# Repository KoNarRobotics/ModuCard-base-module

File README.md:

# ModuCard Base Module

This repository provides a template design for creating modules in the ModuCard system. Each module is designed to seamlessly interface with the [ModuCard backplane](https://github.com/KoNarRobotics/ModuCard-backplane), enabling a modular and expandable robotics platform.

## Used tools:

## Features:

### Power section
- **Input voltage:** 12V from the backplane.  
- **Output voltage:** 3.3V @ 0.5A.

### ST-LINK
- Built-in **ST-LINK** connected to the backplane via USB interface.  
- Enables programming and debugging of the onboard MCU.

### CAN interface
- Two independent CAN buses: **CAN1** and **CAN2**.  
- Both connect with the backplane to facilitate communication between the onboard MCU and other modules in the system.

# How to Create a new module from this template
1. **Create a new repository**
2. **Copy files from this repository** to your new repository.  
3. **Rename the files:**
   - `base-module.kicad_pcb` → `<your-board-name>.kicad_pcb`
   - `base-module.kicad_sch` → `<your-board-name>.kicad_sch`
   - `base-module.kicad_pro` → `<your-board-name>.kicad_pro`
4. **Open the project** in KiCad.  
5. **Update page settings** in the schematic and PCB:
   - Change the **Title** to `ModuCard <your project name>`.  
   - Edit **Comment 2** to include your name in the `<author>` field.
6. Enjoy implementing your project!

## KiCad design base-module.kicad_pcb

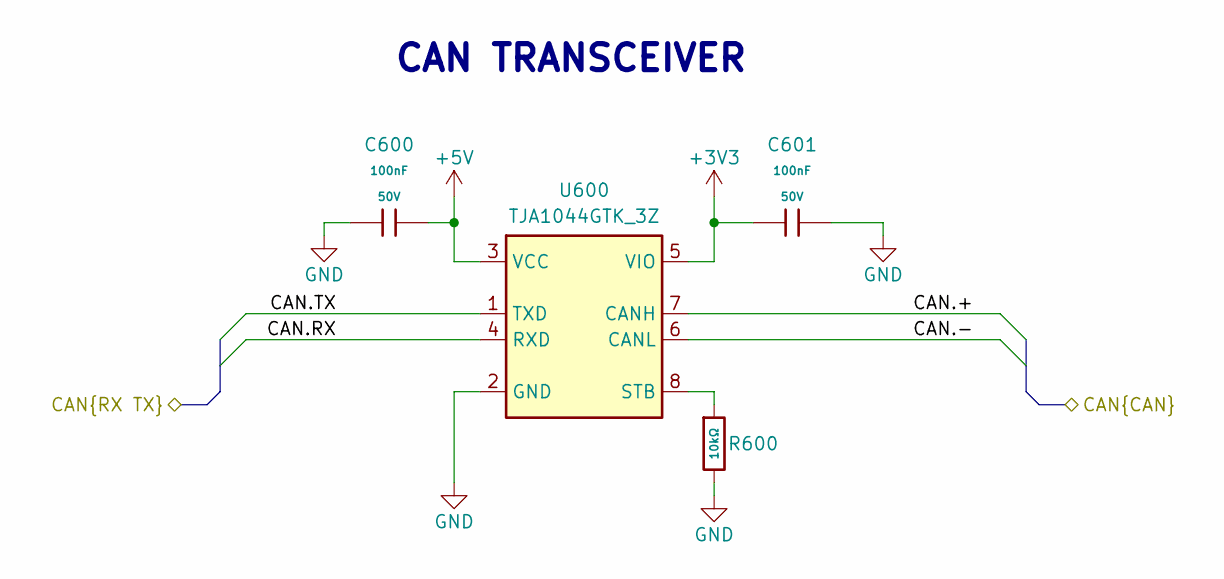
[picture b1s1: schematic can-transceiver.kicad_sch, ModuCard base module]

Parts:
C600, C601: 100nF; C_0402; Voltage Rated 50V; Tolerance ±10%; Part CL05B104KB54PNC; LCSC C307331
R600: 10kΩ; R_0402; Overload Voltage (Max) 50V; Tolerance ±1%; Part 0402WGF1002TCE; LCSC C25744
U600: TJA1044GTK_3Z; HVSON-8-1EP_3x3mm_P0.65mm_EP1.6x2.4mm; Manufacturer_Part_Number TJA1044GTK/3Z

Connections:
+3V3: C601.1, U600.5 (VIO); also elsewhere on the board
+5V: C600.2, U600.3 (VCC); also elsewhere on the board
/Backplane/CAN2.+: U600.7 (CANH); also elsewhere on the board
/Backplane/CAN2.-: U600.6 (CANL); also elsewhere on the board
/CAN transceiver 2/CAN.RX: U600.4 (RXD); also elsewhere on the board
/CAN transceiver 2/CAN.TX: U600.1 (TXD); also elsewhere on the board
GND: C600.1, C601.2, R600.2, U600.2 (GND), U600.9 (EP); also elsewhere on the board
unnamed: R600.1, U600.8 (STB)

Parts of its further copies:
C500, C501: 100nF; C_0402; Voltage Rated 50V; Tolerance ±10%; Part CL05B104KB54PNC; LCSC C307331
R500: 10kΩ; R_0402; Overload Voltage (Max) 50V; Tolerance ±1%; Part 0402WGF1002TCE; LCSC C25744
U500: TJA1044GTK_3Z; HVSON-8-1EP_3x3mm_P0.65mm_EP1.6x2.4mm; Manufacturer_Part_Number TJA1044GTK/3Z

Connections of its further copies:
+3V3: C501.1, U500.5 (VIO); also elsewhere on the board
+5V: C500.2, U500.3 (VCC); also elsewhere on the board
/Backplane/CAN1.+: U500.7 (CANH); also elsewhere on the board
/Backplane/CAN1.-: U500.6 (CANL); also elsewhere on the board
/CAN transceiver 1/CAN.RX: U500.4 (RXD); also elsewhere on the board
/CAN transceiver 1/CAN.TX: U500.1 (TXD); also elsewhere on the board
GND: C500.1, C501.2, R500.2, U500.2 (GND), U500.9 (EP); also elsewhere on the board
unnamed: R500.1, U500.8 (STB)

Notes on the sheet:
CAN TRANSCEIVER

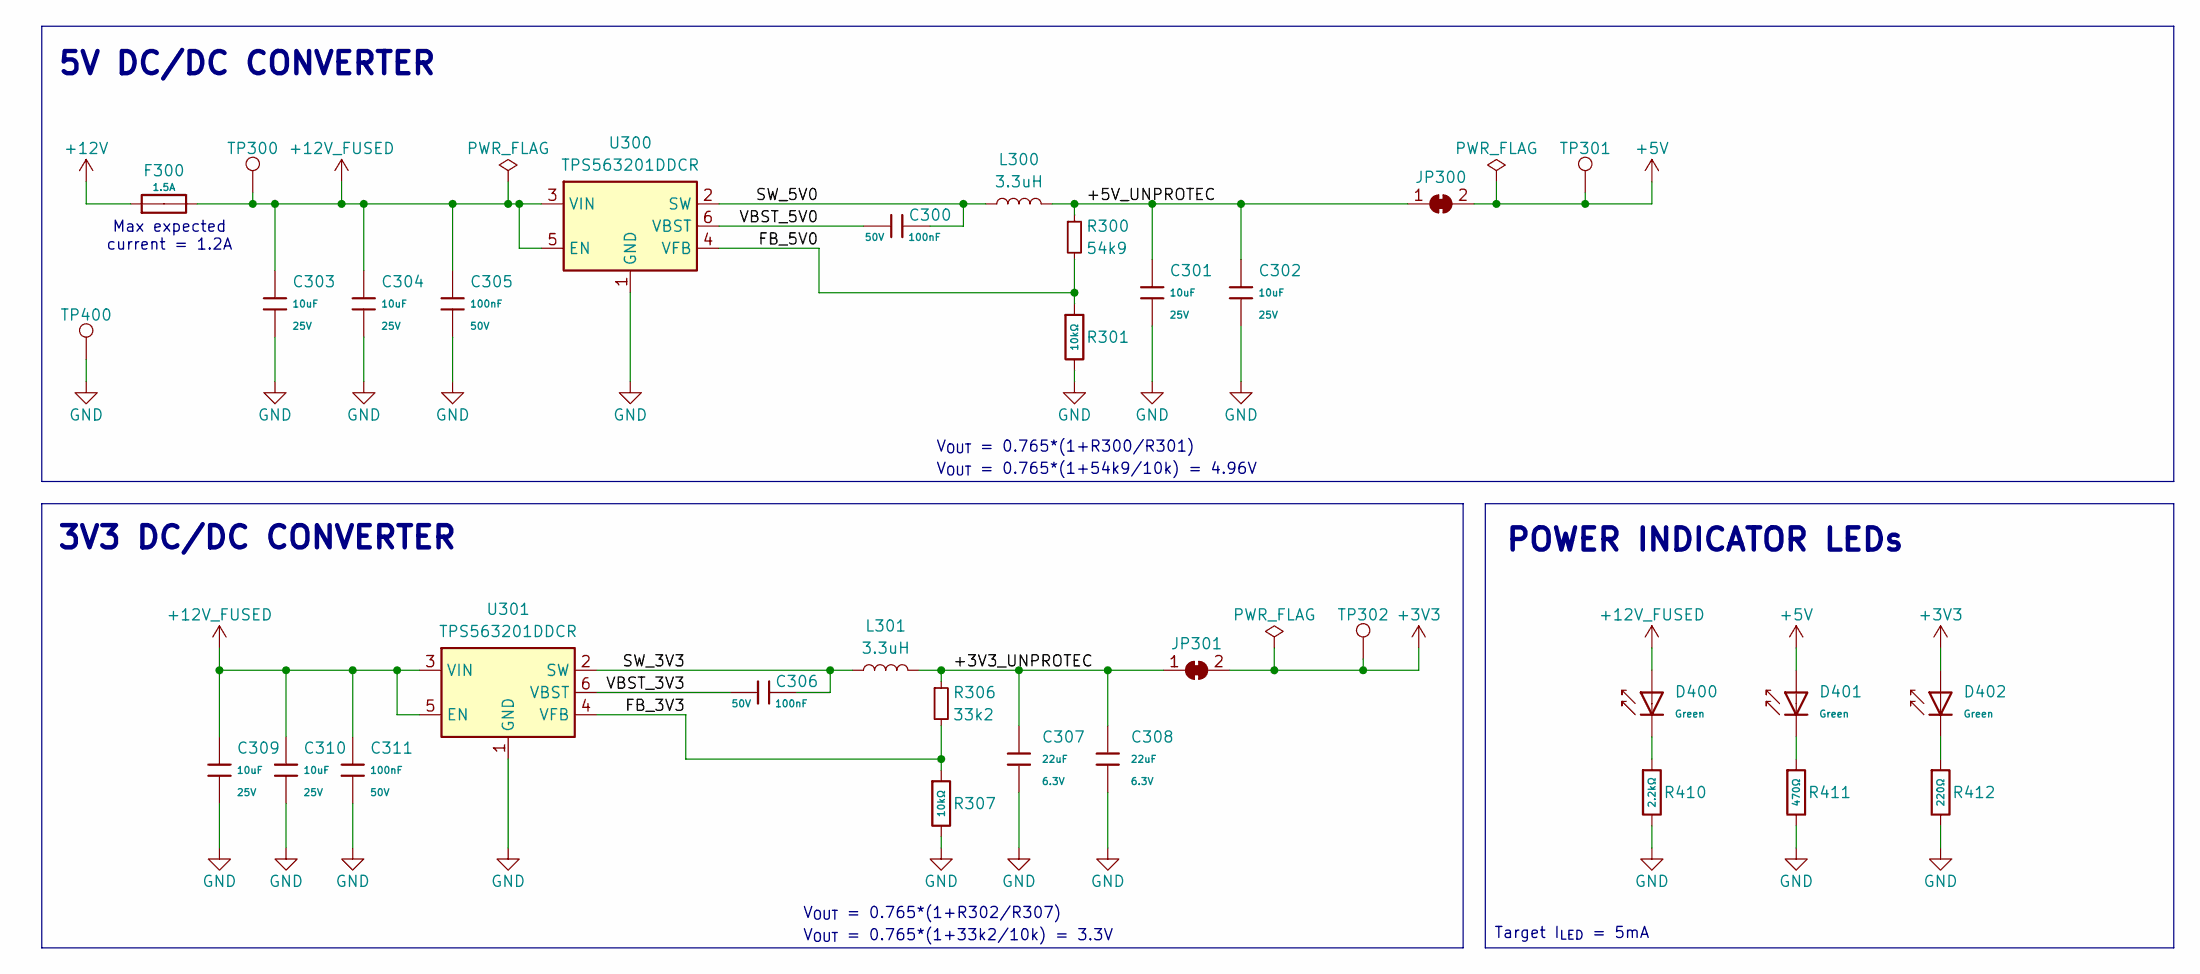
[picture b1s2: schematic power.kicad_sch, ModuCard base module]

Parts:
C300, C305, C306, C311: 100nF; C_0402; Voltage Rated 50V; Tolerance ±10%; Part CL05B104KB54PNC; LCSC C307331
C301, C302, C303, C304, C309, C310: 10uF; C_0603; Voltage Rated 25V; Tolerance ±20%; Part CL10A106MA8NRNC; LCSC C96446
C307, C308: 22uF; C_0603; Voltage Rated 6.3V; Tolerance ±20%; Part CL10A226MQ8NRNC; LCSC C59461
D400, D401, D402: Green; D_0603; Part 19-217/GHC-YR1S2/6T; LCSC C2986059
F300: 1.5A; F_0603; Part F06F1.5; LCSC C2924957
JP300, JP301: Test Buck Vout; SolderJumper-2_P1.3mm_Open_TrianglePad1.0x1.5mm
L300, L301: 3.3uH; L_Changjiang_FXL0420
R300: 54k9; R_0402
R301, R307: 10kΩ; R_0402; Overload Voltage (Max) 50V; Tolerance ±1%; Part 0402WGF1002TCE; LCSC C25744
R306: 33k2; R_0402
R410: 2.2kΩ; R_0402; Overload Voltage (Max) 50V; Tolerance ±1%; Part 0402WGF2201TCE; LCSC C25879
R411: 470Ω; R_0402; Overload Voltage (Max) 50V; Tolerance ±1%; Part 0402WGF4700TCE; LCSC C25117
R412: 220Ω; R_0402; Overload Voltage (Max) 50V; Tolerance ±1%; Part 0402WGF2200TCE; LCSC C25091
TP300, TP301, TP302, TP400: TestPoint; TestPoint_Pad_D1.0mm
U300, U301: TPS563201DDCR; SOT-23-6

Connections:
+3V3: D402.2, JP301.2 (B), TP302.1; also elsewhere on the board
+5V: D401.2, JP300.2 (B), TP301.1; also elsewhere on the board
+12V: F300.1; also elsewhere on the board
+12V_FUSED: C303.1, C304.1, C305.2, C309.1, C310.1, C311.2, D400.2, F300.2, TP300.1, U300.3 (VIN), U300.5 (EN), U301.3 (VIN), U301.5 (EN)
/Power/+3V3_UNPROTEC: C307.1, C308.1, JP301.1 (A), L301.2, R306.1
/Power/+5V_UNPROTEC: C301.1, C302.1, JP300.1 (A), L300.2, R300.1
/Power/FB_3V3: R306.2, R307.1, U301.4 (VFB)
/Power/FB_5V0: R300.2, R301.1, U300.4 (VFB)
/Power/SW_3V3: C306.2, L301.1, U301.2 (SW)
/Power/SW_5V0: C300.2, L300.1, U300.2 (SW)
/Power/VBST_3V3: C306.1, U301.6 (VBST)
/Power/VBST_5V0: C300.1, U300.6 (VBST)
GND: C301.2, C302.2, C303.2, C304.2, C305.1, C307.2, C308.2, C309.2, C310.2, C311.1, R301.2, R307.2, R410.2, R411.2, R412.2, TP400.1, U300.1 (GND), U301.1 (GND); also elsewhere on the board
unnamed: D400.1, R410.1
unnamed: D401.1, R411.1
unnamed: D402.1, R412.1

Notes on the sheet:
V_{OUT} = 0.765*(1+33k2/10k) = 3.3V
Max expected current = 1.2A
V_{OUT} = 0.765*(1+R302/R307)
Target I_{LED} = 5mA
V_{OUT} = 0.765*(1+R300/R301)
5V DC/DC CONVERTER
V_{OUT} = 0.765*(1+54k9/10k) = 4.96V
POWER INDICATOR LEDs
3V3 DC/DC CONVERTER

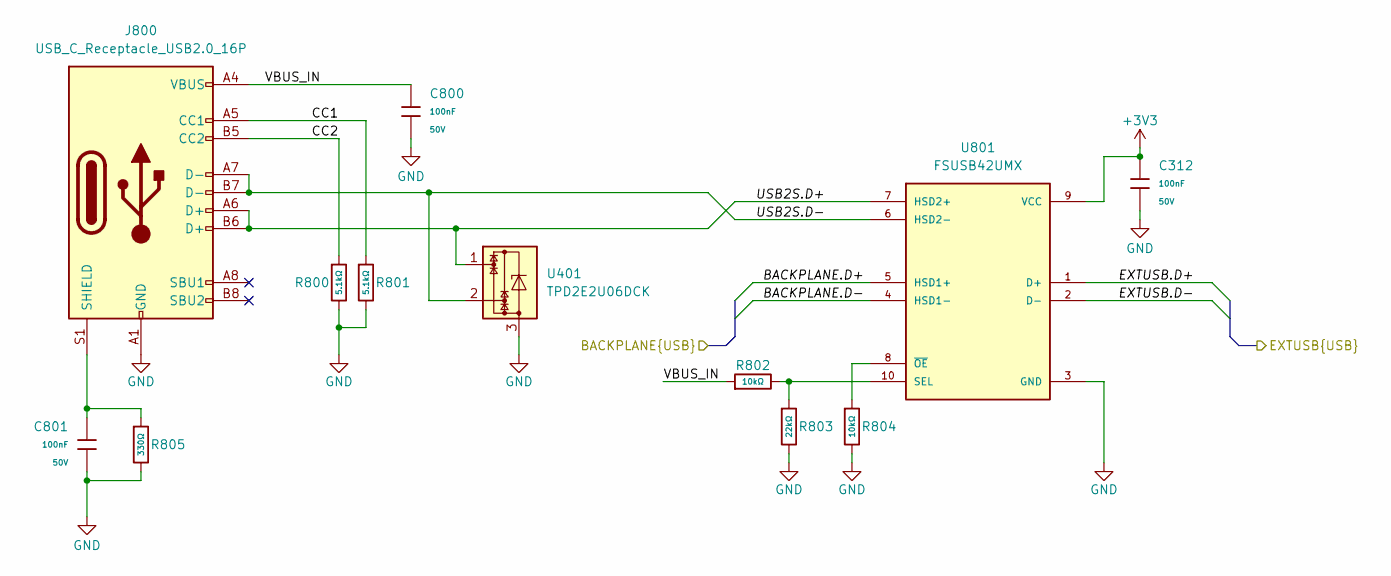
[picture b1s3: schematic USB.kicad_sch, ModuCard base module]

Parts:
C312, C800, C801: 100nF; C_0402; Voltage Rated 50V; Tolerance ±10%; Part CL05B104KB54PNC; LCSC C307331
J800: USB_C_Receptacle_USB2.0_16P; USB_C_Receptacle_GCT_USB4105-xx-A_16P_TopMnt_Horizontal
R800, R801: 5.1kΩ; R_0402; Overload Voltage (Max) 50V; Tolerance ±1%; Part 0402WGF5101TCE; LCSC C25905
R802, R804: 10kΩ; R_0402; Overload Voltage (Max) 50V; Tolerance ±1%; Part 0402WGF1002TCE; LCSC C25744
R803: 22kΩ; R_0402; Overload Voltage (Max) 50V; Tolerance ±1%; Part 0402WGF2202TCE; LCSC C25768
R805: 330Ω; R_0402; Overload Voltage (Max) 50V; Tolerance ±1%; Part 0402WGF3300TCE; LCSC C25104
U401: TPD2E2U06DCK; SOT-323_SC-70
U801: FSUSB42UMX; UQFN-10_1.4x1.8mm_P0.4mm; PARTREV 1.25

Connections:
+3V3: C312.1, U801.9 (VCC); also elsewhere on the board
/Backplane/BACKPLANE.D+: U801.5 (HSD1+); also elsewhere on the board
/Backplane/BACKPLANE.D-: U801.4 (HSD1-); also elsewhere on the board
/USB-hub/USBIN1.D+: U801.1 (D+); also elsewhere on the board
/USB-hub/USBIN1.D-: U801.2 (D-); also elsewhere on the board
/USB/CC1: J800.A5 (CC1), R801.1
/USB/CC2: J800.B5 (CC2), R800.1
/USB/USB2S.D+: J800.A6 (D+), J800.B6 (D+), U401.1, U801.7 (HSD2+)
/USB/USB2S.D-: J800.A7 (D-), J800.B7 (D-), U401.2, U801.6 (HSD2-)
/USB/VBUS_IN: C800.1, J800.A4 (VBUS), J800.A9 (VBUS), J800.B4 (VBUS), J800.B9 (VBUS), R802.1
GND: C312.2, C800.2, C801.2, J800.A1 (GND), J800.A12 (GND), J800.B1 (GND), J800.B12 (GND), R800.2, R801.2, R803.2, R804.2, R805.2, U401.3, U801.3 (GND); also elsewhere on the board
unnamed: C801.1, J800.S1 (SHIELD), R805.1
unnamed: R802.2, R803.1, U801.10 (SEL)
unnamed: R804.1, U801.8 (~OE)

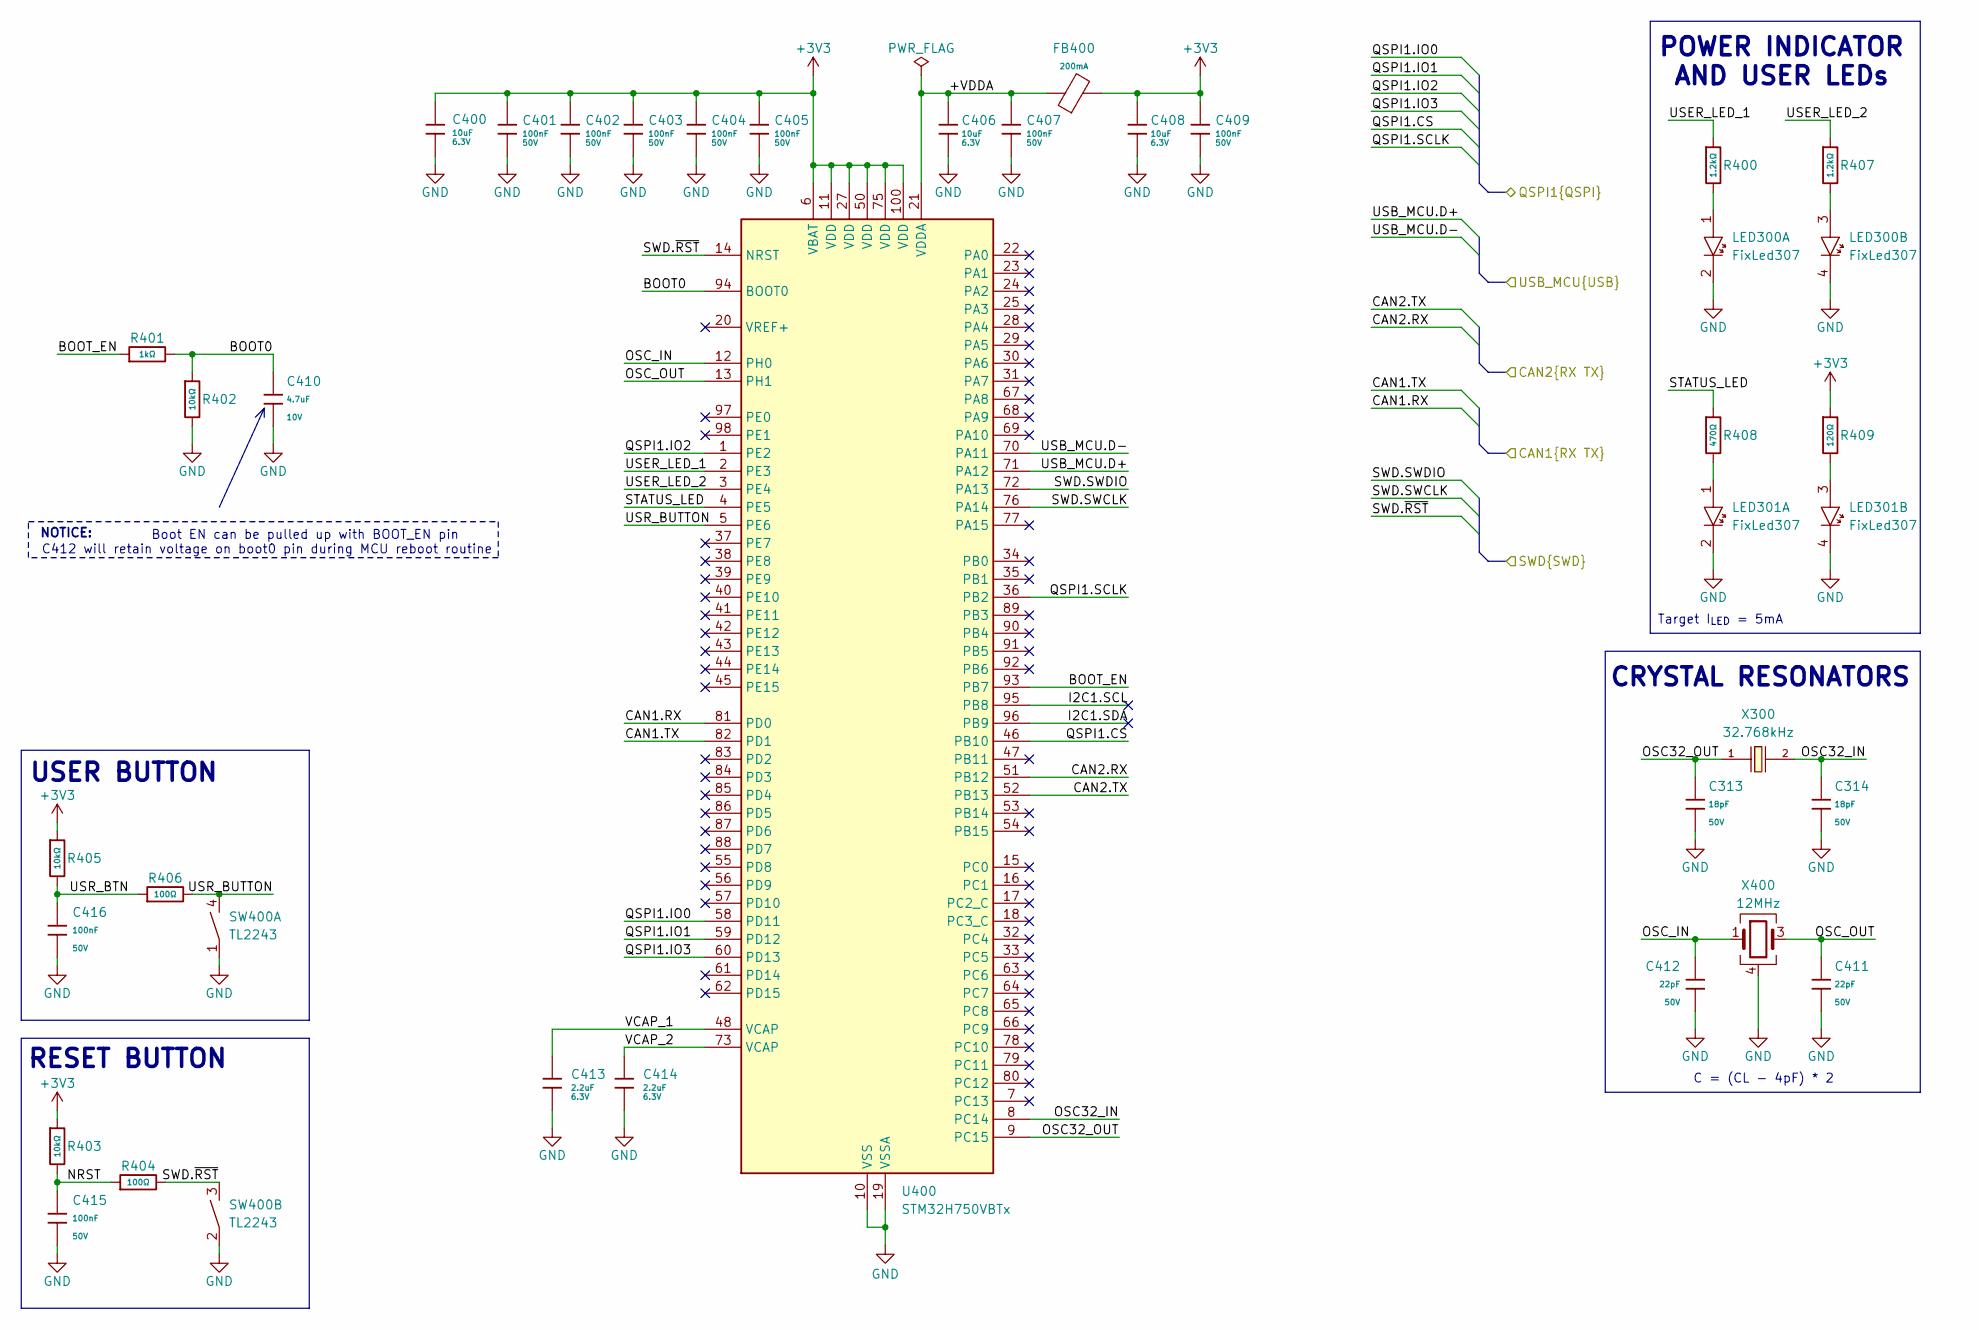
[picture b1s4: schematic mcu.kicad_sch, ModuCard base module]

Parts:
C313, C314: 18pF; C_0402; Voltage Rated 50V; Tolerance ±5%; Part 0402CG180J500NT; LCSC C1549
C400, C406, C408: 10uF; C_0402; Voltage Rated 6.3V; Tolerance ±20%; Part CL05A106MQ5NUNC; LCSC C15525
C401, C402, C403, C404, C405, C407, C409, C415, C416: 100nF; C_0402; Voltage Rated 50V; Tolerance ±10%; Part CL05B104KB54PNC; LCSC C307331
C410: 4.7uF; C_0402; Voltage Rated 10V; Tolerance ±20%; Part CL05A475MP5NRNC; LCSC C23733
C411, C412: 22pF; C_0402; Voltage Rated 50V; Tolerance ±5%; Part 0402CG220J500NT; LCSC C1555
C413, C414: 2.2uF; C_0402; Voltage Rated 6.3V; Tolerance ±20%; Part CL05A225MQ5NSNC; LCSC C12530
FB400: FB_0603; Current Rating 200mA; Tolerance ±25%; Part GZ1608D601TF; LCSC C1002
LED300, LED301: FixLed307
R400, R407: 1.2kΩ; R_0402; Overload Voltage (Max) 50V; Tolerance ±1%; Part 0402WGF1201TCE; LCSC C25862
R401: 1kΩ; R_0402; Overload Voltage (Max) 50V; Tolerance ±1%; Part 0402WGF1001TCE; LCSC C11702
R402, R403, R405: 10kΩ; R_0402; Overload Voltage (Max) 50V; Tolerance ±1%; Part 0402WGF1002TCE; LCSC C25744
R404, R406: 100Ω; R_0402; Overload Voltage (Max) 50V; Tolerance ±1%; Part 0402WGF1000TCE; LCSC C25076
R408: 470Ω; R_0402; Overload Voltage (Max) 50V; Tolerance ±1%; Part 0402WGF4700TCE; LCSC C25117
R409: 120Ω; R_0402; Overload Voltage (Max) 50V; Tolerance ±1%; Part 0402WGF1200TCE; LCSC C25079
SW400: TL2243
U400: STM32H750VBTx; LQFP-100_14x14mm_P0.5mm
X300: Q13FC1350000400; FC-135R_L3.2-W1.5; Frequency Tolerance ±20ppm; Part Q13FC13500004; LCSC C32346
X400: X322512MSB4SI; CRYSTAL-SMD_4P-L3.2-W2.5-BL; Frequency Tolerance ±10ppm; Part X322512MSB4SI; LCSC C9002

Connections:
+3V3: C400.1, C401.1, C402.1, C403.1, C404.1, C405.1, C408.1, C409.1, FB400.2, R403.1, R405.1, R409.1, U400.6 (VBAT), U400.11 (VDD), U400.27 (VDD), U400.50 (VDD), U400.75 (VDD), U400.100 (VDD); also elsewhere on the board
/CAN transceiver 1/CAN.RX: U400.81 (PD0); also elsewhere on the board
/CAN transceiver 1/CAN.TX: U400.82 (PD1); also elsewhere on the board
/CAN transceiver 2/CAN.RX: U400.51 (PB12); also elsewhere on the board
/CAN transceiver 2/CAN.TX: U400.52 (PB13); also elsewhere on the board
/MCU/+VDDA: C406.1, C407.1, FB400.1, U400.21 (VDDA)
/MCU/BOOT0: C410.1, R401.2, R402.1, U400.94 (BOOT0)
/MCU/BOOT_EN: R401.1, U400.93 (PB7)
/MCU/I2C1.SCL: U400.95 (PB8)
/MCU/I2C1.SDA: U400.96 (PB9)
/MCU/NRST: C415.1, R403.2, R404.1
/MCU/OSC32_IN: C314.1, U400.8 (PC14), X300.2
/MCU/OSC32_OUT: C313.1, U400.9 (PC15), X300.1
/MCU/OSC_IN: C412.1, U400.12 (PH0), X400.1
/MCU/OSC_OUT: C411.1, U400.13 (PH1), X400.3
/MCU/QSPI1.CS: U400.46 (PB10); also elsewhere on the board
/MCU/QSPI1.IO0: U400.58 (PD11); also elsewhere on the board
/MCU/QSPI1.IO1: U400.59 (PD12); also elsewhere on the board
/MCU/QSPI1.IO2: U400.1 (PE2); also elsewhere on the board
/MCU/QSPI1.IO3: U400.60 (PD13); also elsewhere on the board
/MCU/QSPI1.SCLK: U400.36 (PB2); also elsewhere on the board
/MCU/STATUS_LED: R408.1, U400.4 (PE5)
/MCU/SWD.SWCLK: U400.76 (PA14); also elsewhere on the board
/MCU/SWD.SWDIO: U400.72 (PA13); also elsewhere on the board
/MCU/SWD.~RST: R404.2, SW400.3, U400.14 (NRST); also elsewhere on the board
/MCU/USB_MCU.D+: U400.71 (PA12); also elsewhere on the board
/MCU/USB_MCU.D-: U400.70 (PA11); also elsewhere on the board
/MCU/USER_LED_1: R400.1, U400.2 (PE3)
/MCU/USER_LED_2: R407.1, U400.3 (PE4)
/MCU/USR_BTN: C416.1, R405.2, R406.1
/MCU/USR_BUTTON: R406.2, SW400.4, U400.5 (PE6)
/MCU/VCAP_1: C413.1, U400.48 (VCAP)
/MCU/VCAP_2: C414.1, U400.73 (VCAP)
GND: C313.2, C314.2, C400.2, C401.2, C402.2, C403.2, C404.2, C405.2, C406.2, C407.2, C408.2, C409.2, C410.2, C411.2, C412.2, C413.2, C414.2, C415.2, C416.2, LED300.2, LED300.4, LED301.2, LED301.4, R402.2, SW400.1, SW400.2, U400.10 (VSS), U400.19 (VSSA), U400.26 (VSS), U400.49 (VSS), U400.74 (VSS), U400.99 (VSS), X400.2, X400.4; also elsewhere on the board
unnamed: LED300.1, R400.2
unnamed: LED300.3, R407.2
unnamed: LED301.1, R408.2
unnamed: LED301.3, R409.2

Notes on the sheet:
Boot EN can be pulled up with BOOT_EN pin C412 will retain voltage on boot0 pin during MCU reboot routine
RESET BUTTON
C = (CL - 4pF) * 2
CRYSTAL RESONATORS
POWER INDICATOR AND USER LEDs
NOTICE:
Target I_{LED} = 5mA
USER BUTTON

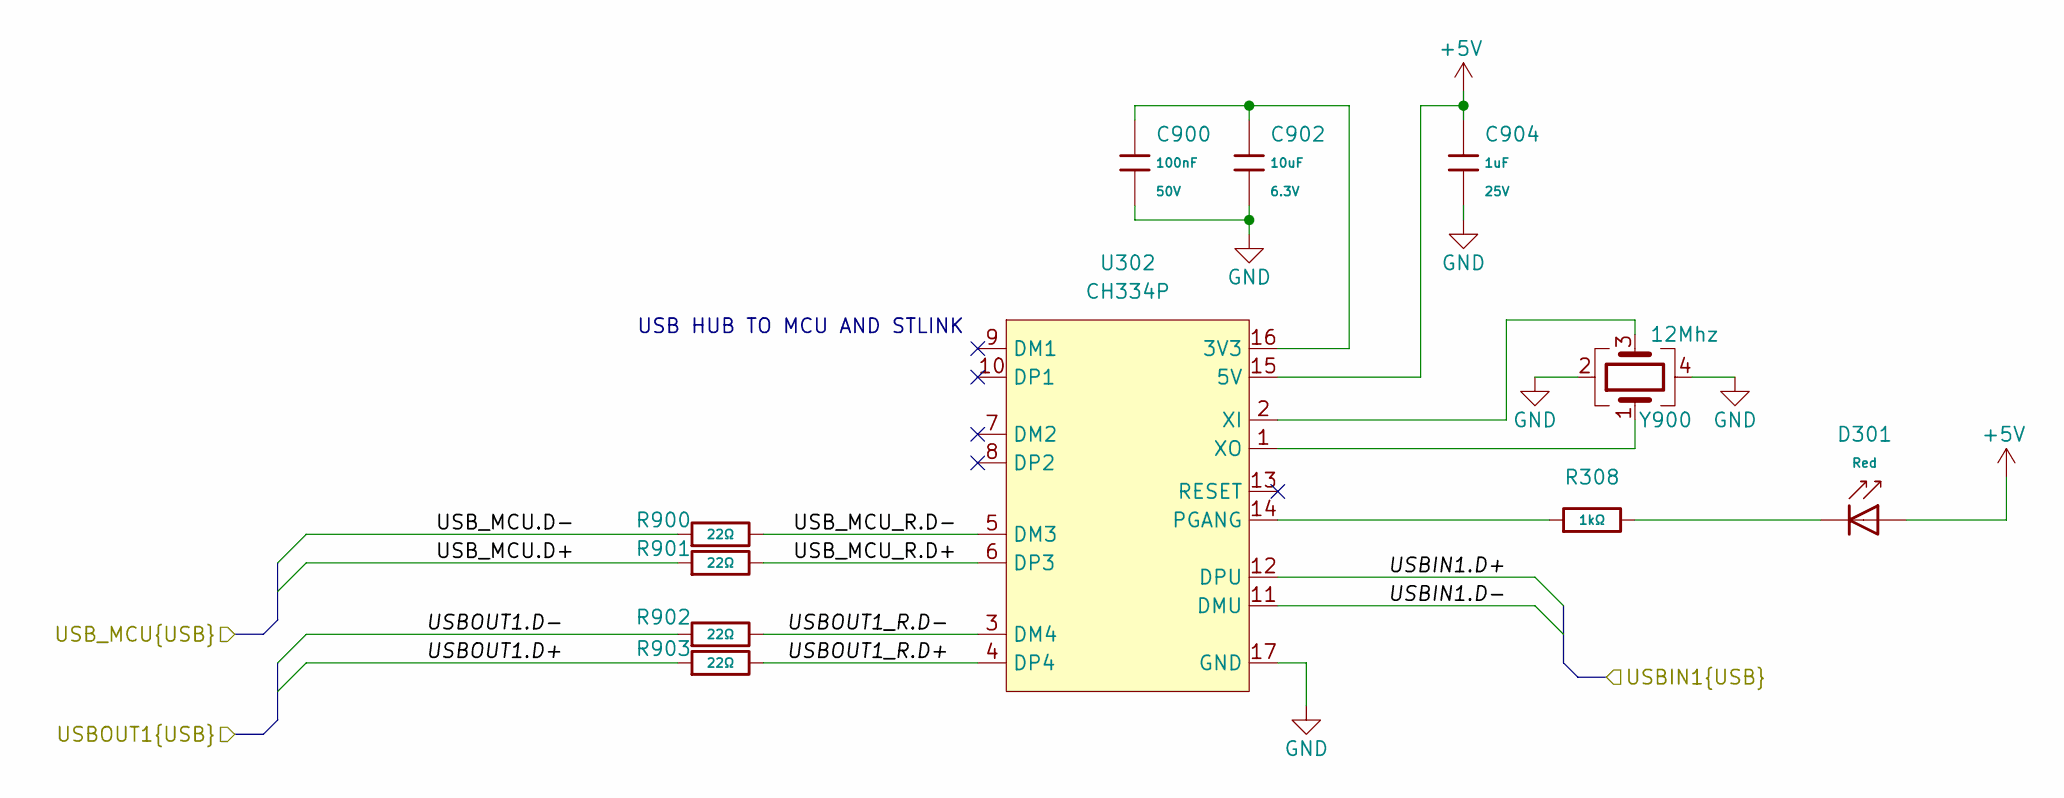
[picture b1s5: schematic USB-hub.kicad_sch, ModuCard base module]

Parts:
C900: 100nF; C_0402; Voltage Rated 50V; Tolerance ±10%; Part CL05B104KB54PNC; LCSC C307331
C902: 10uF; C_0402; Voltage Rated 6.3V; Tolerance ±20%; Part CL05A106MQ5NUNC; LCSC C15525
C904: 1uF; C_0402; Voltage Rated 25V; Tolerance ±10%; Part CL05A105KA5NQNC; LCSC C52923
D301: Red; D_0603; Part KT-0603R; LCSC C2286
R308: 1kΩ; R_0402; Overload Voltage (Max) 50V; Tolerance ±1%; Part 0402WGF1001TCE; LCSC C11702
R900, R901, R902, R903: 22Ω; R_0402; Overload Voltage (Max) 50V; Tolerance ±1%; Part 0402WGF220JTCE; LCSC C25092
U302: CH334P; QFN-16-1EP_3x3mm_P0.5mm_EP1.7x1.7mm
Y900: 12Mhz; Crystal_SMD_3225-4Pin_3.2x2.5mm

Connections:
+5V: C904.1, D301.2, U302.15 (5V); also elsewhere on the board
/MCU/USB_MCU.D+: R901.1; also elsewhere on the board
/MCU/USB_MCU.D-: R900.1; also elsewhere on the board
/ST-LINK/ST-LINK.D+: R903.1; also elsewhere on the board
/ST-LINK/ST-LINK.D-: R902.1; also elsewhere on the board
/USB-hub/USBIN1.D+: U302.12 (DPU); also elsewhere on the board
/USB-hub/USBIN1.D-: U302.11 (DMU); also elsewhere on the board
/USB-hub/USBOUT1_R.D+: R903.2, U302.4 (DP4)
/USB-hub/USBOUT1_R.D-: R902.2, U302.3 (DM4)
/USB-hub/USB_MCU_R.D+: R901.2, U302.6 (DP3)
/USB-hub/USB_MCU_R.D-: R900.2, U302.5 (DM3)
GND: C900.2, C902.2, C904.2, U302.17 (GND), Y900.2, Y900.4; also elsewhere on the board
unnamed: D301.1, R308.2
unnamed: C900.1, C902.1, U302.16 (3V3)
unnamed: R308.1, U302.14 (PGANG)
unnamed: U302.2 (XI), Y900.3
unnamed: U302.1 (XO), Y900.1

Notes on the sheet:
USB HUB TO MCU AND STLINK

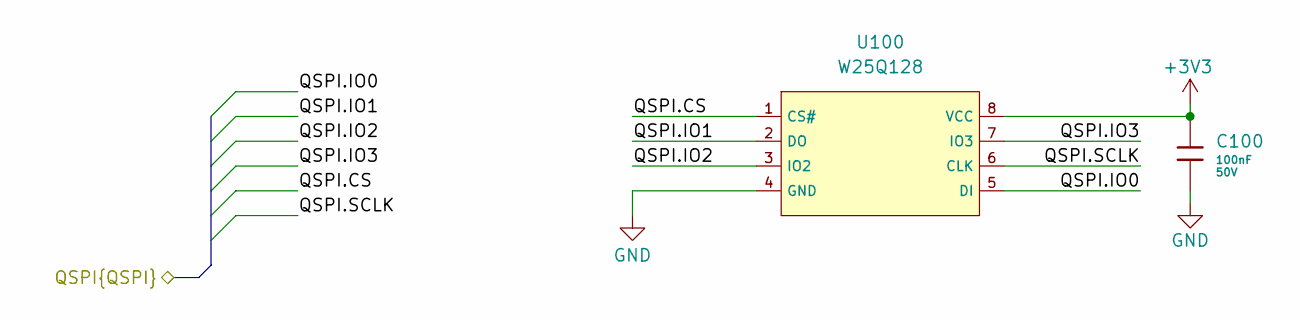
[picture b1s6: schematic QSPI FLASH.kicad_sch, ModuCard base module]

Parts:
C100: 100nF; C_0402; Voltage Rated 50V; Tolerance ±10%; Part CL05B104KB54PNC; LCSC C307331
U100: W25Q128; SOIC-8_L5.3-W5.3-P1.27-LS8.0-BL; Part W25Q128JVSIQ; LCSC C97521

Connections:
+3V3: C100.1, U100.8 (VCC); also elsewhere on the board
/MCU/QSPI1.CS: U100.1 (CS#); also elsewhere on the board
/MCU/QSPI1.IO0: U100.5 (DI); also elsewhere on the board
/MCU/QSPI1.IO1: U100.2 (DO); also elsewhere on the board
/MCU/QSPI1.IO2: U100.3 (IO2); also elsewhere on the board
/MCU/QSPI1.IO3: U100.7 (IO3); also elsewhere on the board
/MCU/QSPI1.SCLK: U100.6 (CLK); also elsewhere on the board
GND: C100.2, U100.4 (GND); also elsewhere on the board

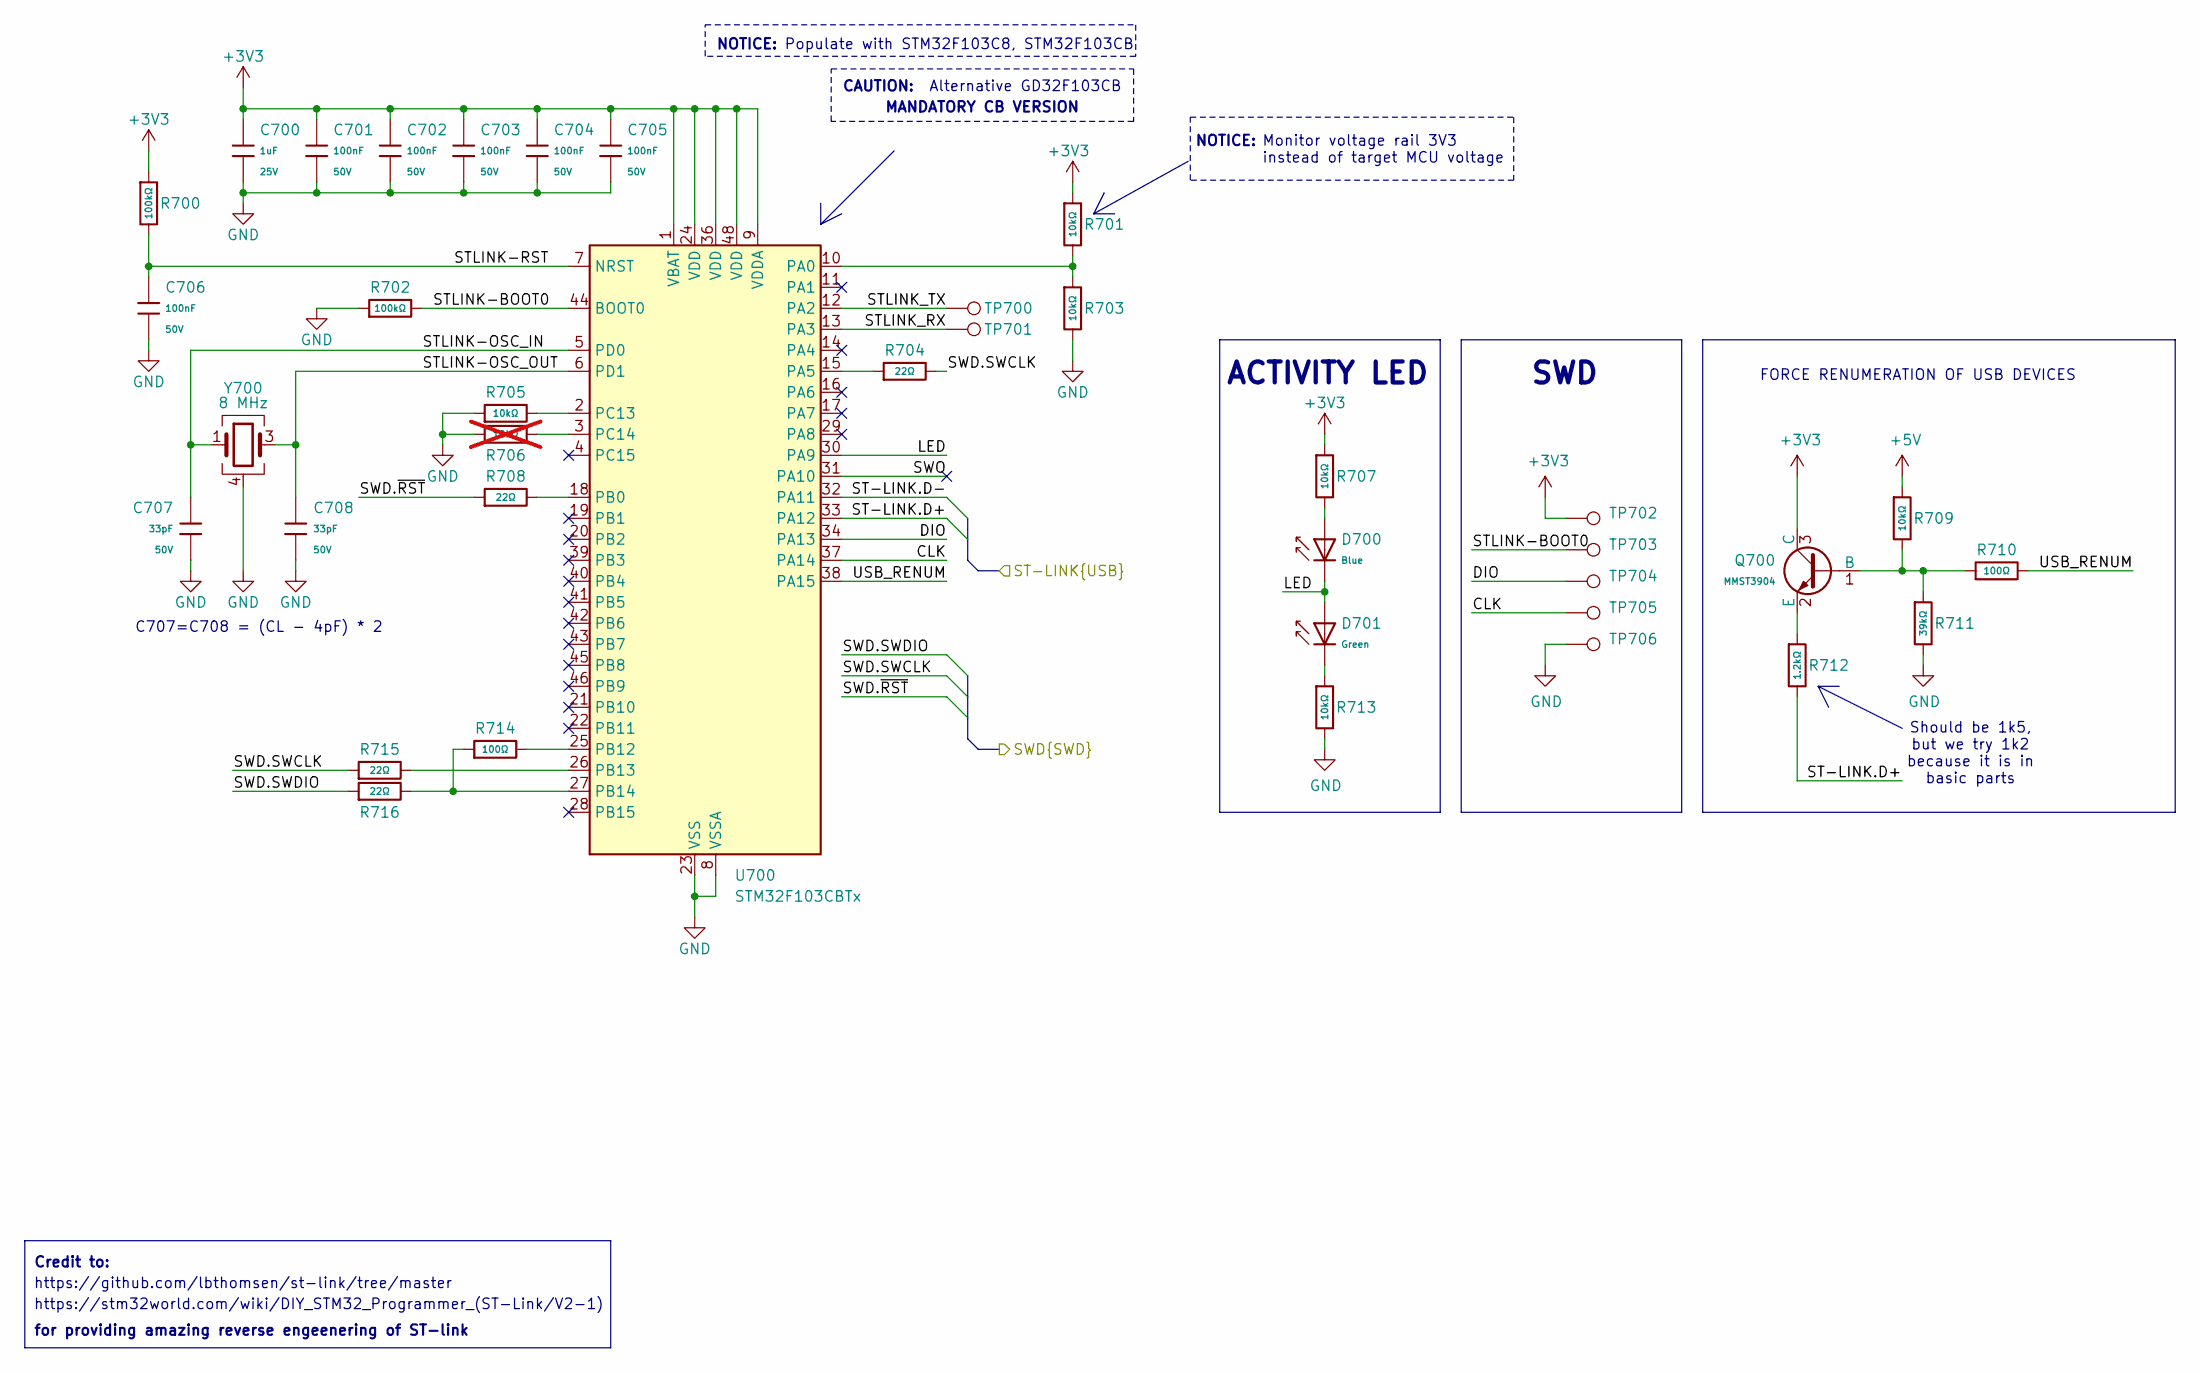
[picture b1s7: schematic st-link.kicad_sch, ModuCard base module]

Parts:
C700: 1uF; C_0402; Voltage Rated 25V; Tolerance ±10%; Part CL05A105KA5NQNC; LCSC C52923
C701, C702, C703, C704, C705, C706: 100nF; C_0402; Voltage Rated 50V; Tolerance ±10%; Part CL05B104KB54PNC; LCSC C307331
C707, C708: 33pF; C_0402; Voltage Rated 50V; Tolerance ±5%; Part 0402CG330J500NT; LCSC C1562
D700: Blue; D_0603; Part 19-217/BHC-ZL1M2RY/6T; LCSC C2986058
D701: Green; D_0603; Part 19-217/GHC-YR1S2/6T; LCSC C2986059
Q700: MMST3904; Q_SOT-323; Part MMST3904; LCSC C22388837
R700, R702: 100kΩ; R_0402; Overload Voltage (Max) 50V; Tolerance ±1%; Part 0402WGF1003TCE; LCSC C25741
R701, R703, R705, R707, R709, R713: 10kΩ; R_0402; Overload Voltage (Max) 50V; Tolerance ±1%; Part 0402WGF1002TCE; LCSC C25744
R704, R708, R715, R716: 22Ω; R_0402; Overload Voltage (Max) 50V; Tolerance ±1%; Part 0402WGF220JTCE; LCSC C25092
R706: 10kΩ; R_0402; Overload Voltage (Max) 50V; Tolerance ±1%; Part 0402WGF1002TCE; LCSC C25744; not fitted
R710, R714: 100Ω; R_0402; Overload Voltage (Max) 50V; Tolerance ±1%; Part 0402WGF1000TCE; LCSC C25076
R711: 39kΩ; R_0402; Overload Voltage (Max) 50V; Tolerance ±1%; Part 0402WGF3902TCE; LCSC C25783
R712: 1.2kΩ; R_0402; Overload Voltage (Max) 50V; Tolerance ±1%; Part 0402WGF1201TCE; LCSC C25862
TP700, TP701: TestPoint; TestPoint_Pad_D1.0mm
TP702, TP703, TP704, TP705, TP706: TestPoint_Pad_D1.0mm
U700: STM32F103CBTx; LQFP-48_7x7mm_P0.5mm
Y700: 8 MHz; CRYSTAL-SMD_4P-L3.2-W2.5-BL; MPN 3225-8.00-20-10-10/4B; LCSC C7424755

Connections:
+3V3: C700.1, C701.1, C702.1, C703.1, C704.1, C705.1, Q700.3 (C), R700.1, R701.1, R707.1, TP702.1, U700.1 (VBAT), U700.9 (VDDA), U700.24 (VDD), U700.36 (VDD), U700.48 (VDD); also elsewhere on the board
+5V: R709.1; also elsewhere on the board
/MCU/SWD.SWCLK: R704.2, R715.1; also elsewhere on the board
/MCU/SWD.SWDIO: R716.1; also elsewhere on the board
/MCU/SWD.~RST: R708.1; also elsewhere on the board
/ST-LINK/CLK: TP705.1, U700.37 (PA14)
/ST-LINK/DIO: TP704.1, U700.34 (PA13)
/ST-LINK/LED: D700.1, D701.2, U700.30 (PA9)
/ST-LINK/ST-LINK.D+: R712.2, U700.33 (PA12); also elsewhere on the board
/ST-LINK/ST-LINK.D-: U700.32 (PA11); also elsewhere on the board
/ST-LINK/STLINK-BOOT0: R702.2, TP703.1, U700.44 (BOOT0)
/ST-LINK/STLINK-OSC_IN: C707.1, U700.5 (PD0), Y700.1
/ST-LINK/STLINK-OSC_OUT: C708.1, U700.6 (PD1), Y700.3
/ST-LINK/STLINK-RST: C706.1, R700.2, U700.7 (NRST)
/ST-LINK/STLINK_RX: TP701.1, U700.13 (PA3)
/ST-LINK/STLINK_TX: TP700.1, U700.12 (PA2)
/ST-LINK/SWO: U700.31 (PA10)
/ST-LINK/USB_RENUM: R710.2, U700.38 (PA15)
GND: C700.2, C701.2, C702.2, C703.2, C704.2, C705.2, C706.2, C707.2, C708.2, R702.1, R703.2, R705.1, R706.1, R711.2, R713.2, TP706.1, U700.8 (VSSA), U700.23 (VSS), U700.35 (VSS), U700.47 (VSS), Y700.2, Y700.4; also elsewhere on the board
unnamed: D700.2, R707.2
unnamed: D701.1, R713.1
unnamed: Q700.1 (B), R709.2, R710.1, R711.1
unnamed: Q700.2 (E), R712.1
unnamed: R701.2, R703.1, U700.10 (PA0)
unnamed: R704.1, U700.15 (PA5)
unnamed: R708.2, U700.18 (PB0)
unnamed: R714.2, U700.25 (PB12)
unnamed: R715.2, U700.26 (PB13)
unnamed: R714.1, R716.2, U700.27 (PB14)
unnamed: R705.2, U700.2 (PC13)
unnamed: R706.2, U700.3 (PC14)

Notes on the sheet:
Alternative GD32F103CB
SWD
NOTICE:
C707=C708 = (CL - 4pF) * 2
Monitor voltage rail 3V3 instead of target MCU voltage
https://stm32world.com/wiki/DIY_STM32_Programmer_(ST-Link/V2-1)
CAUTION:
Populate with STM32F103C8, STM32F103CB
Should be 1k5, but we try 1k2 because it is in basic parts
ACTIVITY LED
for providing amazing reverse engeenering of ST-link
MANDATORY CB VERSION
FORCE RENUMERATION OF USB DEVICES
https://github.com/lbthomsen/st-link/tree/master
Credit to:
